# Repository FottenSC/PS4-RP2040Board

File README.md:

# Project 5001

Bill of materials:<br/>
1x <a href="https://www.digikey.com/en/products/detail/adafruit-industries-llc/5302/15794634">Adafruit KB2040 board</a><br/>
1x <a href="https://www.digikey.com/en/products/detail/w%C3%BCrth-elektronik/430451035836/5209030">6.2mm tactile switch</a><br/>
2x <a href="https://www.digikey.com/en/products/detail/c-k/THB001P/11687191">Joysticks</a><br/>

Forked from BeckyStern More info:
https://beckystern.com/?p=114849

### License
me do think you should read the license file full credit to BeckyStern

Sauces:
https://github.com/CountParadox/RP2040-Zero-Kicad

lol:
https://www.instructables.com/Salvage-USB-Gear-from-Discarded-Laptops/

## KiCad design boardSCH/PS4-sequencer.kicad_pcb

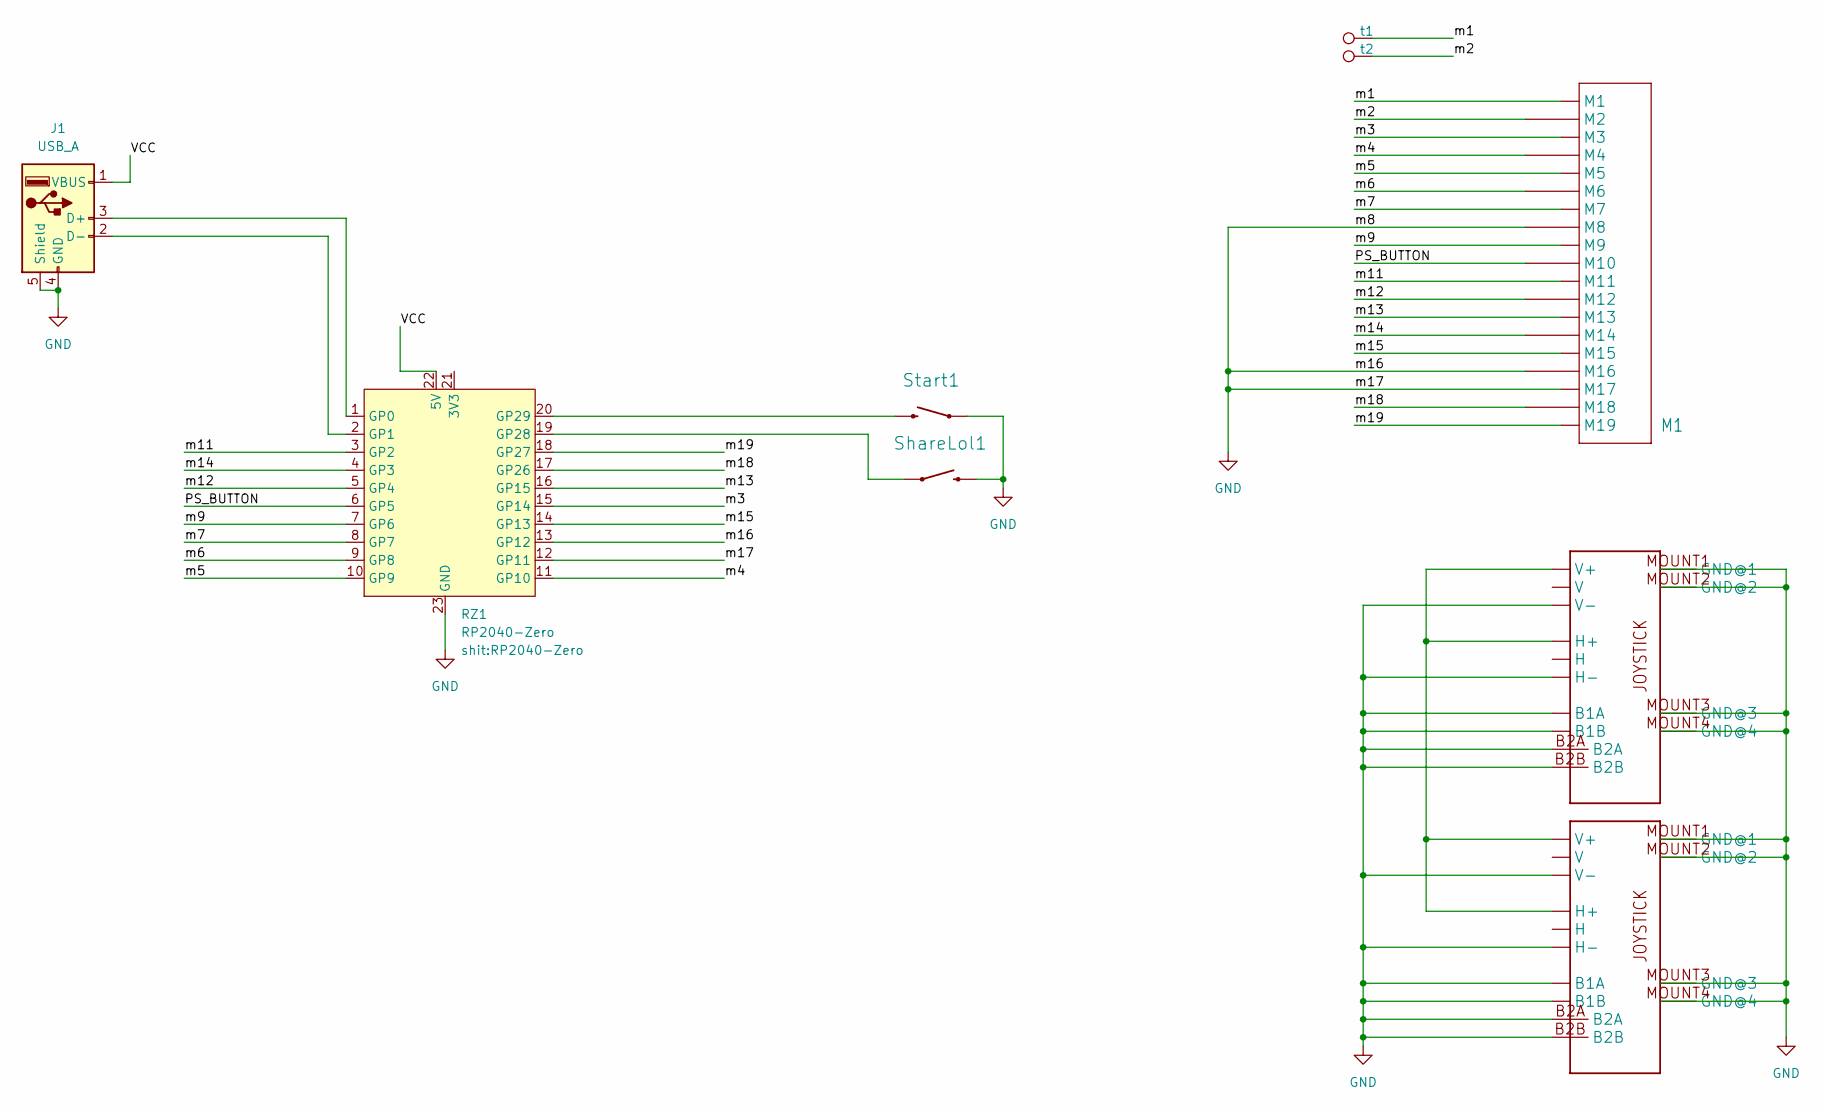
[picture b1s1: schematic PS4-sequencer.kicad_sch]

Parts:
J1: USB_A; USB_A_Female_UE27AC54100
M1: PS4MEMBRANE_vf.7upxoABMT86JB5hzkim21Q
RZ1: RP2040-Zero
ShareLol1: TACTILE_SWITCH_SMD_3.6MM_vf.7upxoABMT86JB5hzkim21Q
Start1: TACTILE_SWITCH_SMD_3.6MM_vf.7upxoABMT86JB5hzkim21Q
U1, U2: PS4JOYSTICK_vf.IaU3msWoRHeUc8tSE1TGOQ
t1, t2: TestPoint_Pad_1.5x1.5mm

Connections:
/PS_BUTTON: M1.10 (M10), RZ1.6 (GP5)
/VCC: J1.1 (VBUS), RZ1.22 (5V)
/m1: M1.1 (M1), t1.1
/m2: M1.2 (M2), t2.1
/m3: M1.3 (M3), RZ1.15 (GP14)
/m4: M1.4 (M4), RZ1.11 (GP10)
/m5: M1.5 (M5), RZ1.10 (GP9)
/m6: M1.6 (M6), RZ1.9 (GP8)
/m7: M1.7 (M7), RZ1.8 (GP7)
/m9: M1.9 (M9), RZ1.7 (GP6)
/m11: M1.11 (M11), RZ1.3 (GP2)
/m12: M1.12 (M12), RZ1.5 (GP4)
/m13: M1.13 (M13), RZ1.16 (GP15)
/m14: M1.14 (M14), RZ1.4 (GP3)
/m15: M1.15 (M15), RZ1.14 (GP13)
/m18: M1.18 (M18), RZ1.17 (GP26)
/m19: M1.19 (M19), RZ1.18 (GP27)
GND: J1.4 (GND), J1.5 (Shield), M1.8 (M8), M1.16 (M16), M1.17 (M17), RZ1.12 (GP11), RZ1.13 (GP12), RZ1.23 (GND), ShareLol1.1 (2), ShareLol1.4 (2), Start1.2 (1), Start1.3 (1), U1.B1A, U1.B1B, U1.B2A, U1.B2B, U1.H3 (H-), U1.MOUNT1 (GND@1), U1.MOUNT2 (GND@2), U1.MOUNT3 (GND@3), U1.MOUNT4 (GND@4), U1.V3 (V-), U2.B1A, U2.B1B, U2.B2A, U2.B2B, U2.H3 (H-), U2.MOUNT1 (GND@1), U2.MOUNT2 (GND@2), U2.MOUNT3 (GND@3), U2.MOUNT4 (GND@4), U2.V3 (V-)
unnamed: J1.3 (D+), RZ1.1 (GP0)
unnamed: J1.2 (D-), RZ1.2 (GP1)
unnamed: RZ1.19 (GP28), ShareLol1.2 (1), ShareLol1.3 (1)
unnamed: RZ1.20 (GP29), Start1.1 (2), Start1.4 (2)
unnamed: U1.H1 (H+), U1.V1 (V+), U2.H1 (H+), U2.V1 (V+)

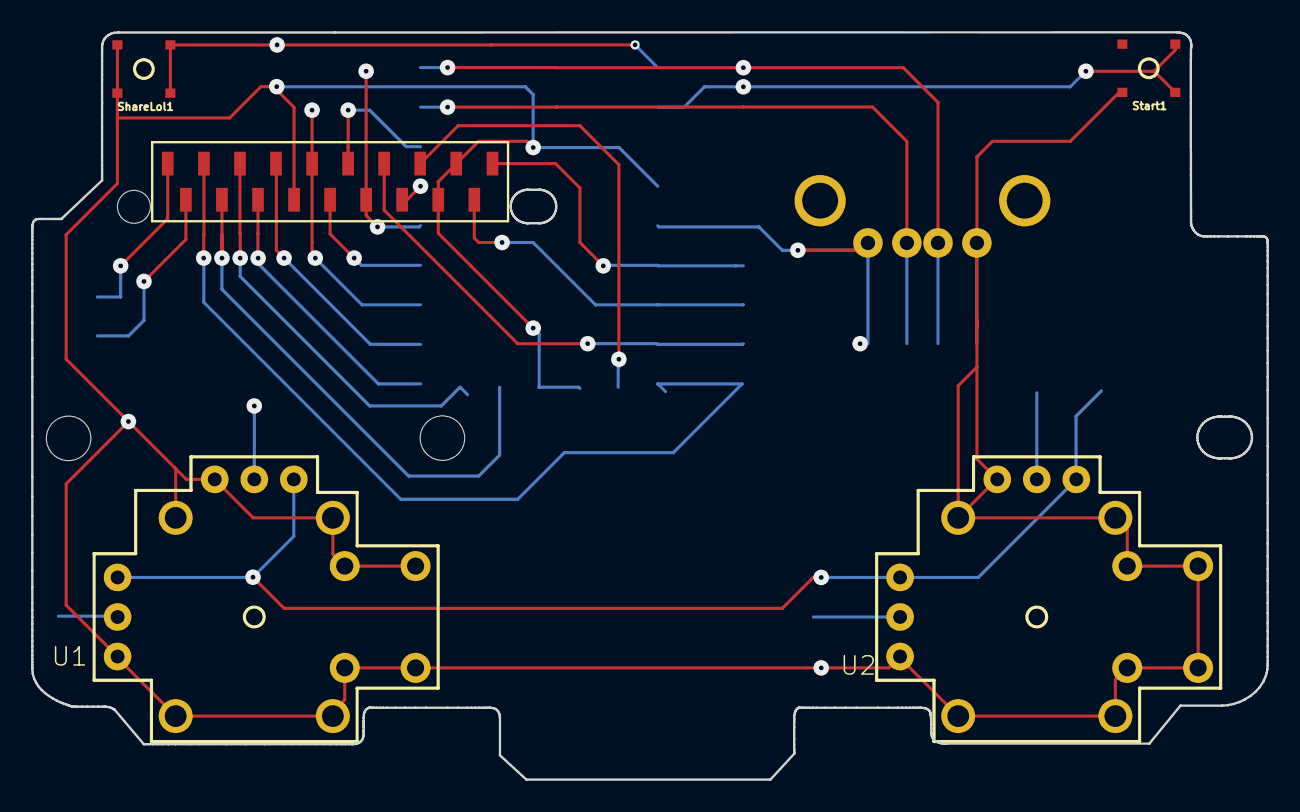
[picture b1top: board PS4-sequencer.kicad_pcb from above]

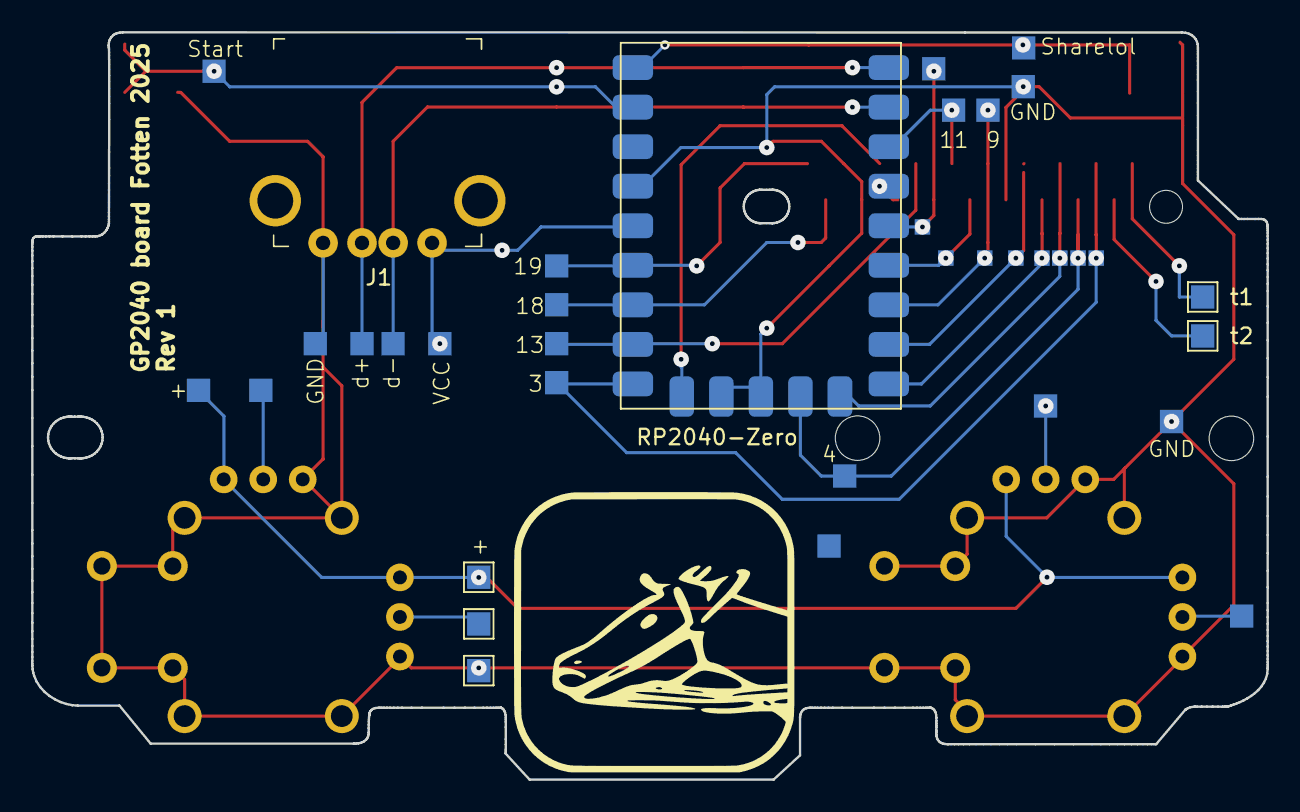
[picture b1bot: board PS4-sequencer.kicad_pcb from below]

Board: 2 copper layers, 79.3 x 48.0 mm, 9 parts (4 on the bottom side), 23 nets.

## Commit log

2025-06-23 init
